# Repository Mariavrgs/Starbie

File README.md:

# Starbie

Um bichinho virtual numa placa de circuito impresso feita no KiCad. O Starbie anda numa tela OLED, reage a toques nos botões e ao movimento da placa, e mostra a temperatura e a umidade do ambiente.

## O que ele faz

- O bichinho vagueia pela tela. A tela normal não mostra nome nem valores.
- **Botão 1, primeiro toque:** abre o menu radial.
- **Inclinar a placa com o menu aberto:** move a bolinha, e cada direção corresponde a uma ação.
- **Botão 1, segundo toque:** escolhe a ação destacada.
- **Botão 2:** mostra ou esconde as estatísticas (alegria, energia, fome, temperatura e umidade).
- **Sacudir a placa:** faz o Starbie tremer e acorda ele do soninho.

Ações do menu: `NAP` (cima), `PLAY` (direita), `FEED` (baixo) e `DANCE` (esquerda).

## Hardware

| Peça | Função |
|---|---|
| Seeed XIAO ESP32-C3 (U1) | Microcontrolador |
| Display OLED 0,96" 128x64 I2C (J1) | Tela do bichinho |
| MPU6050 em header de 8 pinos (J2) | Acelerômetro, para o menu por inclinação e para sacudir |
| DHT11 (U2) com resistor de 10 kΩ (R1) | Temperatura e umidade |
| 2 botões Cherry MX (SW1 e SW2) | Controles |

### Ligações

| Função | Pino do XIAO | GPIO |
|---|---|---|
| SDA (OLED e MPU6050) | D4 | 6 |
| SCL (OLED e MPU6050) | D5 | 7 |
| Dados do DHT11 | D1 | 3 |
| Botão 1 | D2 | 4 |
| Botão 2 | D3 | 5 |

Os botões ligam o pino ao GND e usam `INPUT_PULLUP` no firmware.

## Estrutura do repositório

```
.
├── kicad2.kicad_pro        Projeto do KiCad
├── kicad2.kicad_sch        Esquemático
├── kicad2.kicad_pcb        Placa (com zona de GND em B.Cu)
├── fp-lib-table            Tabela de bibliotecas de footprints
├── Imported_Parts.pretty/  Footprints do OLED e do XIAO
├── Gerbers/                Arquivos de fabricação
└── Firmware/
    └── Starbie/
        └── Starbie.ino     Código para a IDE do Arduino
```

## Placa

Projetada no KiCad 10. O roteamento está completo, e o DRC passa sem erros, só com dois avisos de footprint (J1 e U1 diferentes da cópia da biblioteca `Imported Parts`), que não afetam a fabricação.

Para fabricar, use os arquivos da pasta `Gerbers/`: os `.gbr` de cada camada e o arquivo de furação `.drl`.

## Firmware

O programa é um único sketch do Arduino, sem PlatformIO e sem biblioteca personalizada.

1. Instale a [IDE do Arduino](https://www.arduino.cc/en/software).
2. Em **File > Preferences**, adicione em *Additional boards manager URLs*:
   `https://espressif.github.io/arduino-esp32/package_esp32_index.json`
3. Em **Tools > Board > Boards Manager**, instale **esp32 by Espressif Systems**.
4. Em **Tools > Board > esp32**, escolha **XIAO_ESP32C3**.
5. Em **Sketch > Include Library > Manage Libraries**, instale:
   - Adafruit GFX Library
   - Adafruit SSD1306
   - Adafruit MPU6050
   - DHT sensor library

   Se pedir dependências, escolha *Install all*.
6. Abra `Firmware/Starbie/Starbie.ino`, mantendo a pasta `Starbie` e o arquivo com o mesmo nome, e clique em **Upload**.

### Personalizar

As opções ficam no topo do `Starbie.ino`:

- Pinos: `I2C_SDA_PIN`, `I2C_SCL_PIN`, `DHT_PIN`, `BUTTON_ONE_PIN`, `BUTTON_TWO_PIN`.
- `USE_DHT11 = false` se a sua versão não tiver o sensor.
- `TILT_SWAP_XY`, `TILT_INVERT_X` e `TILT_INVERT_Y` se a bolinha do menu se mover na direção errada.
- O vetor `MENU_ITEMS` muda os rótulos e os efeitos do menu.
- `PET_SPRITE` é o bitmap 32x32 do bichinho. Dá para gerar o seu no [image2cpp](https://javl.github.io/image2cpp/).

## Estado do projeto

O firmware compila para a placa XIAO_ESP32C3. Ainda não foi testado numa placa montada.

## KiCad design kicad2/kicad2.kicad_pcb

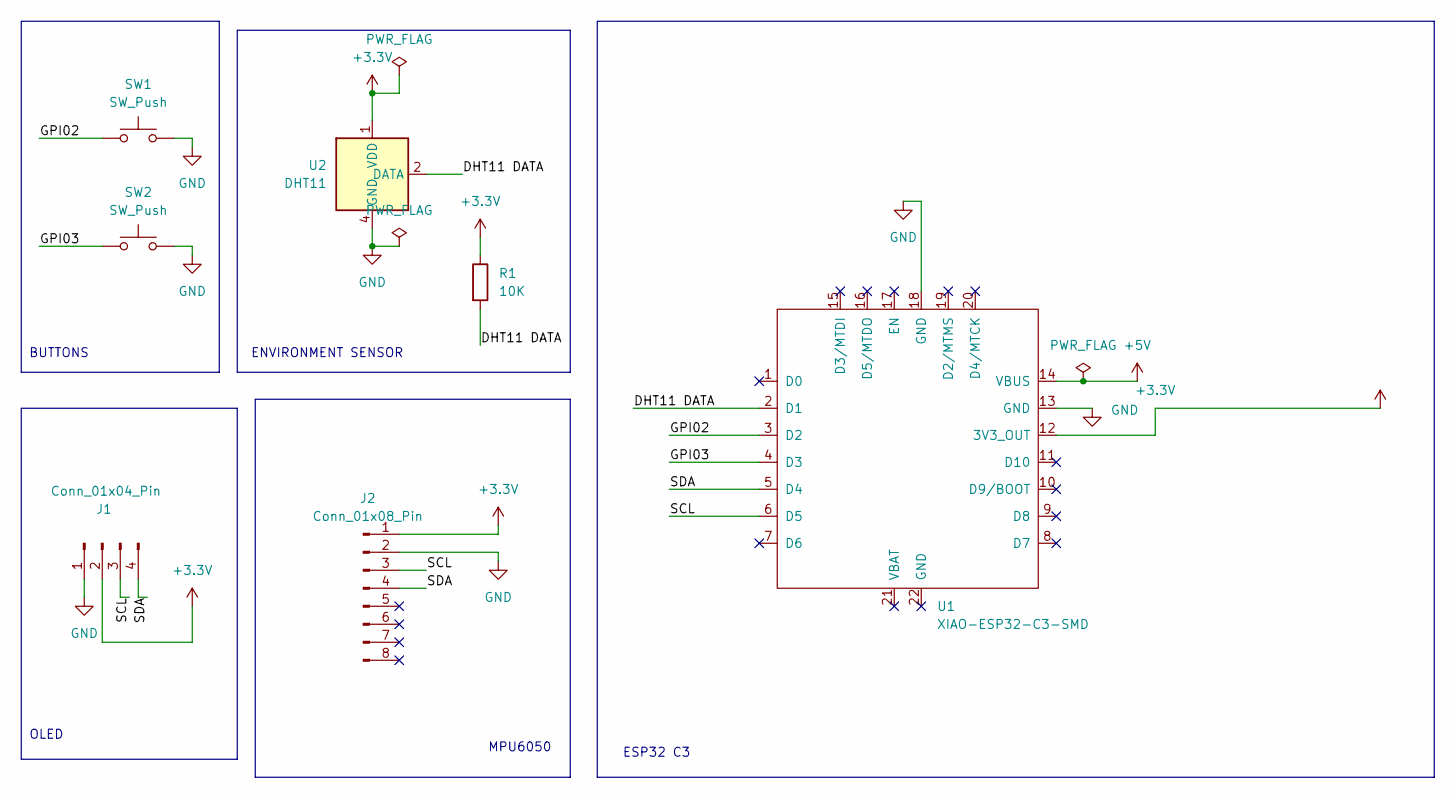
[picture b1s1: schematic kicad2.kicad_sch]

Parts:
J1: Conn_01x04_Pin; Display_128x64_096_I2C
J2: Conn_01x08_Pin; PinHeader_1x08_P2.54mm_Vertical
R1: 10K; R_Axial_DIN0204_L3.6mm_D1.6mm_P7.62mm_Horizontal
SW1, SW2: SW_Push; SW_Cherry_MX_1.00u_PCB
U1: XIAO-ESP32-C3-SMD
U2: DHT11; Aosong_DHT11_5.5x12.0_P2.54mm

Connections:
+3.3V: J1.2, J2.1, R1.1, U1.12 (3V3_OUT), U2.1 (VDD)
+5V: U1.14 (VBUS)
/DHT11 DATA: R1.2, U1.2 (D1), U2.2 (DATA)
/GPI02: SW1.1, U1.3 (D2)
/GPI03: SW2.1, U1.4 (D3)
/SCL: J1.3, J2.3, U1.6 (D5)
/SDA: J1.4, J2.4, U1.5 (D4)
GND: J1.1, J2.2, SW1.2, SW2.2, U1.13 (GND), U1.18 (GND), U2.4 (GND)

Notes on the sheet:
BUTTONS
OLED
ENVIRONMENT SENSOR
MPU6050
ESP32 C3

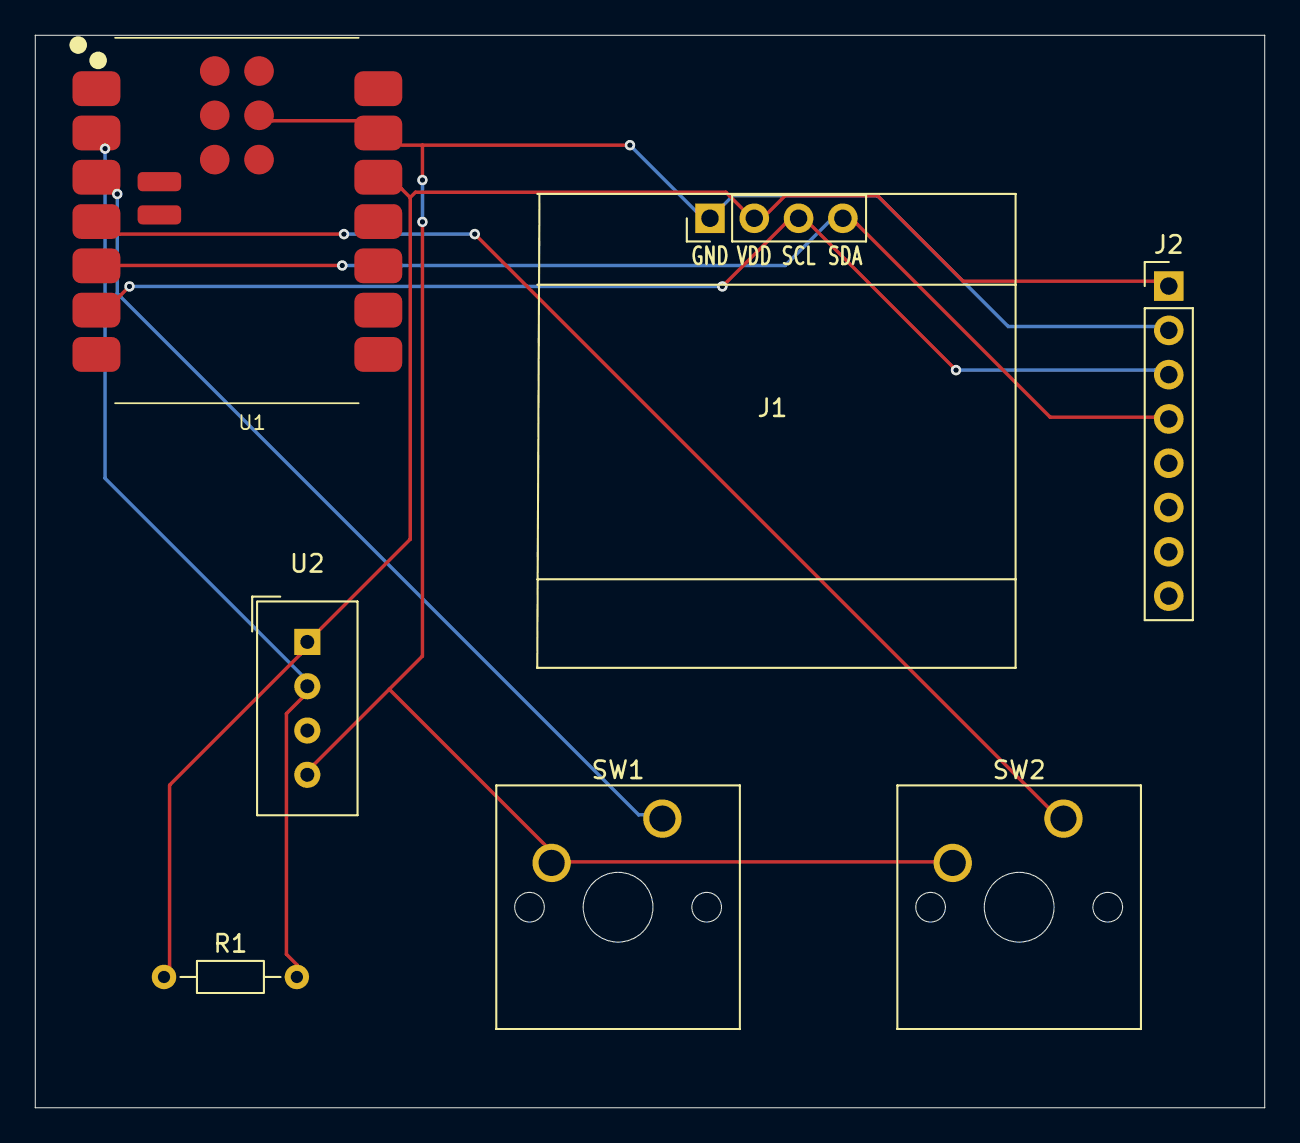
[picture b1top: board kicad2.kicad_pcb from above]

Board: 2 copper layers, 70.5 x 61.5 mm, 7 parts (0 on the bottom side), 7 nets.

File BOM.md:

# Starbie – lista de materiais (BOM)

| Semana | Tier | Verba para peças |
|---|---|---|
| Semana 1 | Tier 1 | $30,00 |

## Peças

| Ref. | Qtd. | Peça | Detalhes | Preço unit. | Link |
|---|---|---|---|---|---|
| U1 | 1 | Seeed Studio XIAO ESP32-C3 | Microcontrolador. Footprint `XIAO-ESP32-C3-SMD`, soldado direto na placa | _preencha_ | _preencha_ |
| J1 | 1 | Display OLED 0,96", 128x64, I2C | Controlador SSD1306, 4 pinos (GND, VDD, SCL, SDA) | _preencha_ | _preencha_ |
| J2 | 1 | Barra de pinos 1x8, passo 2,54 mm | Para encaixar o módulo MPU6050 | _preencha_ | _preencha_ |
| — | 1 | Módulo MPU6050 (acelerômetro e giroscópio) | Encaixa no J2. Usado para o menu por inclinação e para sacudir | _preencha_ | _preencha_ |
| U2 | 1 | Sensor DHT11 | Temperatura e umidade, 4 pinos, passo 2,54 mm | _preencha_ | _preencha_ |
| R1 | 1 | Resistor 10 kΩ | Pull-up do DHT11, axial, passo 7,62 mm | _preencha_ | _preencha_ |
| SW1, SW2 | 2 | Switch mecânico Cherry MX (ou compatível) | Botões 1 e 2, footprint `SW_Cherry_MX_1.00u_PCB` | _preencha_ | _preencha_ |
| — | 1 | PCB `kicad2` | Gerbers na pasta `Gerbers/`. Fabricantes costumam vender no mínimo 5 unidades | _preencha_ | _preencha_ |

## Opcionais

| Peça | Para quê |
|---|---|
| Keycaps MX (2) | Dar acabamento aos botões |
| Cabo USB-C | Programar e alimentar o XIAO |
| Soquete de pinos para o display | Poder trocar o OLED sem dessoldar |

## Total

| Item | Valor |
|---|---|
| Soma das peças | _preencha_ |
| Frete e impostos | _preencha_ |
| **Total** | _preencha_ |
| Verba disponível | $30,00 |

> Os preços e os links ficam em branco porque variam por loja e por região. Preencha com o que for comprar e confira se o total cabe na verba.
